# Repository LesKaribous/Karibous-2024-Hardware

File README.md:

# Karibous-2024-Hardware
Hardware du robot des Karibous pour la Coupe de Robotique (Eurobot) 2024

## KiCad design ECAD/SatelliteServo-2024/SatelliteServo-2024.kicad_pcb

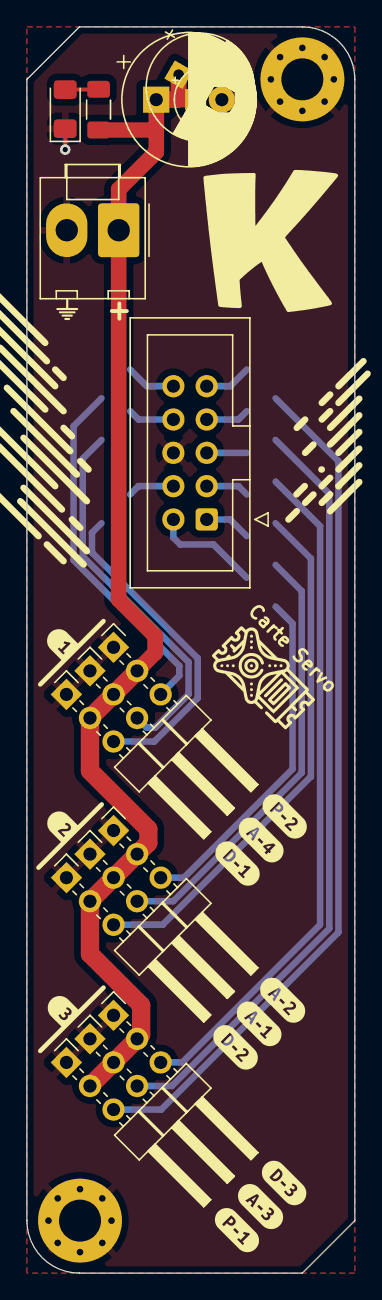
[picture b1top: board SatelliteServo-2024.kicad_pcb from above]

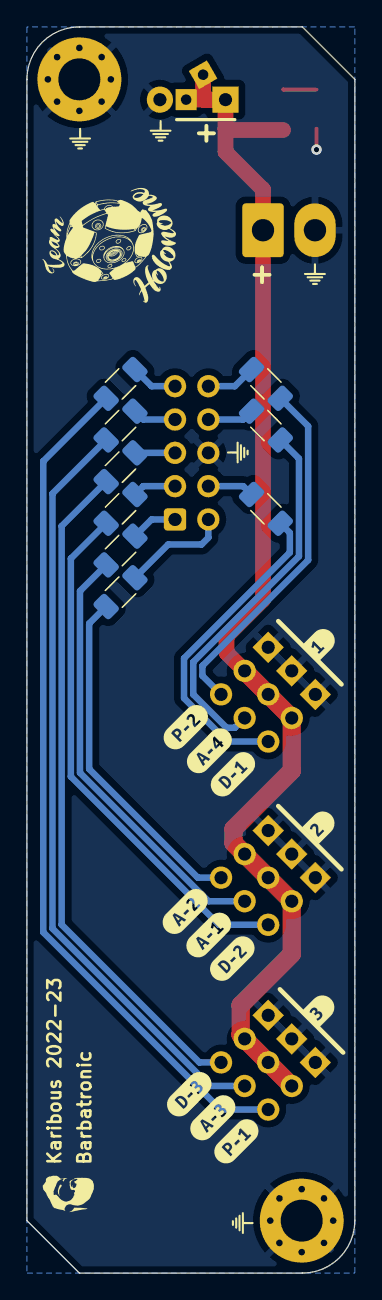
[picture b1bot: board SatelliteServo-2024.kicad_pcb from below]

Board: 2 copper layers, 25.0 x 95.0 mm, 51 parts (21 on the bottom side), 21 nets.

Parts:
C1: C_Polarized_Small; CP_Radial_D10.0mm_P5.00mm
C2: C_Polarized_Small; CP_Radial_D8.0mm_P3.80mm
C3: C_Polarized_Small; CP_Radial_D5.0mm_P2.00mm
D1: LED_Small; LED_1206_3216Metric_Pad1.42x1.75mm_HandSolder
H1, H2: MountingHole_Pad; MountingHole_3.2mm_M3_Pad_Via
J1: Conn_02x05_Odd_Even; IDC-Header_2x05_P2.54mm_Vertical
J2: Conn_01x02; Molex_KK-396_A-41791-0002_1x02_P3.96mm_Vertical
J3, J4, J5, J6, J7, J8, J9, J10, J11: Conn_01x03; PinHeader_3x01_P2.54mm_Horizontal
R1: R_Small; R_1206_3216Metric_Pad1.30x1.75mm_HandSolder
R2, R3, R4, R5, R6, R7, R8, R9, R10: 220; R_1206_3216Metric_Pad1.30x1.75mm_HandSolder
kibuzzard-634F1A03, kibuzzard-634F1A03#2: G***; kibuzzard-634F1A03
kibuzzard-634F1A09, kibuzzard-634F1A09#2: G***; kibuzzard-634F1A09
kibuzzard-634F1B5B: G***; kibuzzard-634F1B5B
kibuzzard-634F1B38: G***; kibuzzard-634F1B38
kibuzzard-634F1B56: G***; kibuzzard-634F1B56
kibuzzard-634F1BA4: G***; kibuzzard-634F1BA4
kibuzzard-634F1BAB: G***; kibuzzard-634F1BAB
kibuzzard-634F1BB2: G***; kibuzzard-634F1BB2
kibuzzard-634F18D6, kibuzzard-634F18D6#2: G***; kibuzzard-634F18D6
kibuzzard-634F18FE, kibuzzard-634F18FE#2: G***; kibuzzard-634F18FE
kibuzzard-634F19A0, kibuzzard-634F19A0#2: G***; kibuzzard-634F19A0
kibuzzard-634F19A7, kibuzzard-634F19A7#2: G***; kibuzzard-634F19A7
kibuzzard-634F19AD, kibuzzard-634F19AD#2: G***; kibuzzard-634F19AD
kibuzzard-634F19FE, kibuzzard-634F19FE#2: G***; kibuzzard-634F19FE
kibuzzard-634F1907, kibuzzard-634F1907#2: G***; kibuzzard-634F1907

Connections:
+5VP: C1.1, C2.1, C3.1, J2.1, J3.2, J4.2, J5.2, J6.2, J7.2, J8.2, J9.2, J10.2, J11.2, R1.1
GND: C1.2, C2.2, C3.2, D1.1 (K), H1.1, H2.1, J1.6, J2.2, J3.1, J4.1, J5.1, J6.1, J7.1, J8.1, J9.1, J10.1, J11.1
IO_A_1: J1.1, R7.2
IO_A_2: J1.2, R8.2
IO_A_3: J1.7, R9.2
IO_A_4: J1.8, R10.2
IO_D_1: J1.4, R2.2
IO_D_2: J1.3, R3.2
IO_D_3: J1.5, R4.2
IO_P_1: J1.9, R5.2
IO_P_2: J1.10, R6.2
unnamed: D1.2 (A), R1.2
unnamed: J3.3, R2.1
unnamed: J4.3, R3.1
unnamed: J5.3, R4.1
unnamed: J6.3, R7.1
unnamed: J7.3, R5.1
unnamed: J8.3, R6.1
unnamed: J9.3, R8.1
unnamed: J10.3, R9.1
unnamed: J11.3, R10.1

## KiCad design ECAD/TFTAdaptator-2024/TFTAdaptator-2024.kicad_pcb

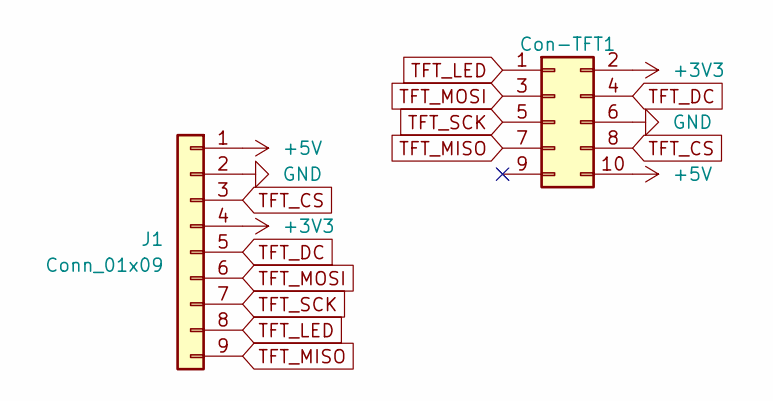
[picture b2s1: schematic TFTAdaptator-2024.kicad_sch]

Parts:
Con-TFT1: Conn_02x05_Odd_Even; IDC-Header_2x05_P2.54mm_Vertical
J1: Conn_01x09; PinSocket_1x09_P2.54mm_Vertical

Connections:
+3V3: Con-TFT1.2, J1.4
+5V: Con-TFT1.10, J1.1
GND: Con-TFT1.6, J1.2
TFT_CS: Con-TFT1.8, J1.3
TFT_DC: Con-TFT1.4, J1.5
TFT_LED: Con-TFT1.1, J1.8
TFT_MISO: Con-TFT1.7, J1.9
TFT_MOSI: Con-TFT1.3, J1.6
TFT_SCK: Con-TFT1.5, J1.7

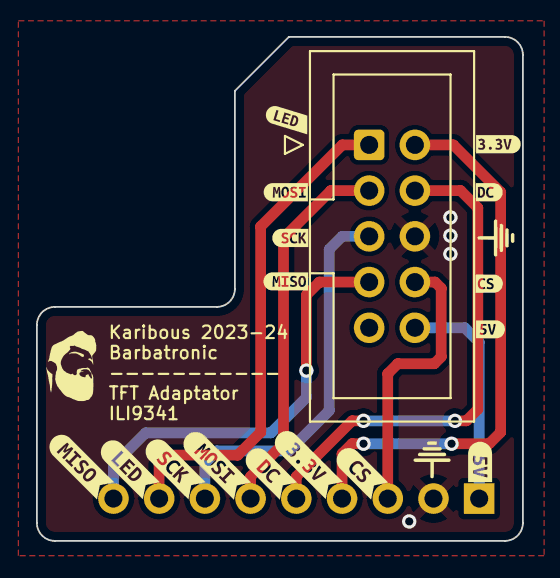
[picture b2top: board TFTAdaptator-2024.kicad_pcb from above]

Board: 2 copper layers, 27.0 x 28.0 mm, 18 parts (1 on the bottom side), 9 nets.

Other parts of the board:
kibuzzard-64E9C8A2: G***; kibuzzard-64E9C8A2
kibuzzard-64E9C89C: G***; kibuzzard-64E9C89C
kibuzzard-64E9C866: G***; kibuzzard-64E9C866
kibuzzard-64E9C890: G***; kibuzzard-64E9C890
kibuzzard-64E9C897: G***; kibuzzard-64E9C897
kibuzzard-64E9CBF9: G***; kibuzzard-64E9CBF9
kibuzzard-64E9CDB6: G***; kibuzzard-64E9CDB6
kibuzzard-64E9CDBF: G***; kibuzzard-64E9CDBF
kibuzzard-64E9CDD4: G***; kibuzzard-64E9CDD4
kibuzzard-64E9CDE3: G***; kibuzzard-64E9CDE3
kibuzzard-64E9CE8E: G***; kibuzzard-64E9CE8E
kibuzzard-64E9CE87: G***; kibuzzard-64E9CE87
kibuzzard-64E9CE93: G***; kibuzzard-64E9CE93
kibuzzard-64E9CEBE: G***; kibuzzard-64E9CEBE
kibuzzard-64E9CFC9: G***; kibuzzard-64E9CFC9
kibuzzard-64933136: G***; kibuzzard-64933136

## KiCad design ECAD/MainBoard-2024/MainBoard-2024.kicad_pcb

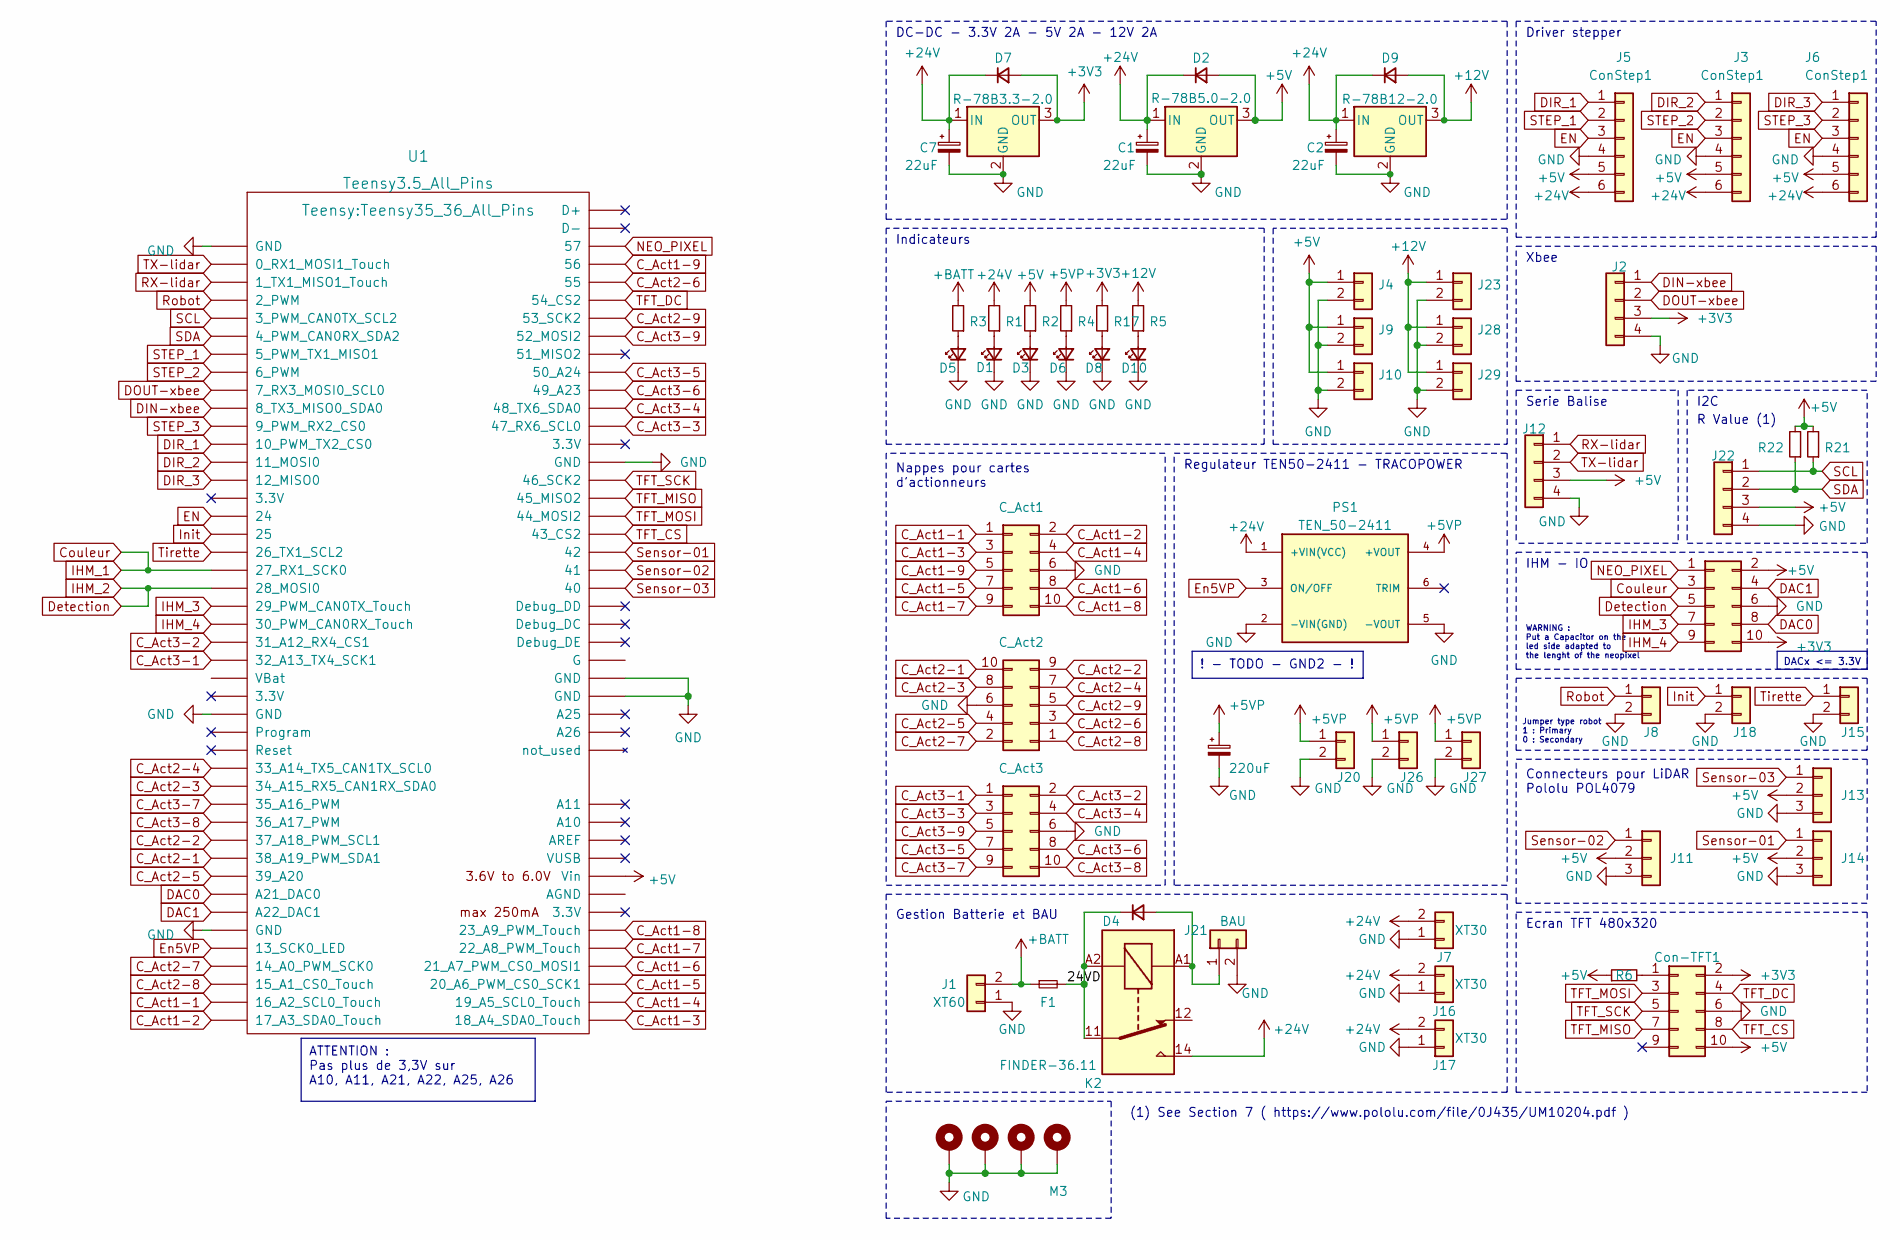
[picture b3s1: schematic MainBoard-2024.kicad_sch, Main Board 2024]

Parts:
C1, C2, C7: 22uF; CP_Elec_5x5.4
C6: 220uF; CP_Radial_D8.0mm_P3.80mm
C_Act1, C_Act2, C_Act3: Conn_02x05_Odd_Even; IDC-Header_2x05_P2.54mm_Vertical
Con-TFT1: Conn_02x05_Odd_Even; IDC-Header_2x05_P2.54mm_Vertical
D1, D3, D5, D6, D8, D10: LED_Small; LED_1206_3216Metric_Pad1.42x1.75mm_HandSolder
D2, D4, D7, D9: D_Small; D_SMA_Handsoldering
F1: Fuse_Small; Fuseholder_Blade_Mini_Keystone_3568
H1, H2, H3, H4: M3; MountingHole_3.2mm_M3_Pad_Via
IHM-IO1: Conn_02x05_Odd_Even; IDC-Header_2x05_P2.54mm_Vertical
J1: XT60; AMASS_XT60-M_1x02_P7.20mm_Vertical
J2, J12, J22: Conn_01x04; Molex_KK-254_AE-6410-04A_1x04_P2.54mm_Vertical
J3, J5, J6: ConStep1; Molex_KK-254_AE-6410-06A_1x06_P2.54mm_Vertical
J4, J9, J10, J15, J18, J23, J28, J29: Conn_01x02; Molex_KK-254_AE-6410-02A_1x02_P2.54mm_Vertical
J7, J16, J17: XT30; AMASS_XT30U-F_1x02_P5.0mm_Vertical
J8: Conn_01x02; PinHeader_1x02_P2.54mm_Vertical
J11, J13, J14: Conn_01x03; Molex_KK-254_AE-6410-03A_1x03_P2.54mm_Vertical
J20, J21, J26, J27: BAU; Molex_KK-396_A-41791-0002_1x02_P3.96mm_Vertical
K2: FINDER-36.11; Relay_SPDT_Finder_36.11
PS1: TEN_50-2411; CONV_TEN_50-2411; PARTREV February 3, 2021
R1, R2, R3, R4, R5, R6, R17, R21, R22: R_Small; R_1206_3216Metric_Pad1.30x1.75mm_HandSolder
U1: Teensy3.5_All_Pins; Teensy35_36_All_Pins
U2: R-78B3.3-2.0; Converter_DCDC_RECOM_R-78B-2.0_THT
U3: R-78B12-2.0; Converter_DCDC_RECOM_R-78B-2.0_THT
U4: R-78B5.0-2.0; Converter_DCDC_RECOM_R-78B-2.0_THT

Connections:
+3V3: Con-TFT1.2, D7.2 (A), IHM-IO1.10, J2.3, R17.2, U2.3 (OUT)
+5V: Con-TFT1.10, D2.2 (A), IHM-IO1.2, J3.5, J4.1, J5.5, J6.5, J9.1, J10.1, J11.2, J12.3, J13.2, J14.2, J22.3, R2.2, R6.1, R21.2, R22.2, U1.53 (Vin), U4.3 (OUT)
+5VP: C6.1, J20.1, J26.1, J27.1, PS1.4 (+VOUT), R4.2
+12V: D9.2 (A), J23.1, J28.1, J29.1, R5.2, U3.3 (OUT)
+24V: C1.1, C2.1, C7.1, D2.1 (K), D7.1 (K), D9.1 (K), J3.6, J5.6, J6.6, J7.2, J16.2, J17.2, K2.14, PS1.1 (+VIN(VCC)), R1.2, U2.1 (IN), U3.1 (IN), U4.1 (IN)
+BATT: F1.1, J1.2, R3.2
/24VD: D4.1 (K), F1.2, K2.11, K2.A2
C_Act1-1: C_Act1.1, U1.43 (16_A2_SCL0_Touch)
C_Act1-2: C_Act1.2, U1.44 (17_A3_SDA0_Touch)
C_Act1-3: C_Act1.3, U1.45 (18_A4_SDA0_Touch)
C_Act1-4: C_Act1.4, U1.46 (19_A5_SCL0_Touch)
C_Act1-5: C_Act1.7, U1.47 (20_A6_PWM_CS0_SCK1)
C_Act1-6: C_Act1.8, U1.48 (21_A7_PWM_CS0_MOSI1)
C_Act1-7: C_Act1.9, U1.49 (22_A8_PWM_Touch)
C_Act1-8: C_Act1.10, U1.50 (23_A9_PWM_Touch)
C_Act1-9: C_Act1.5, U1.85 (56)
C_Act2-1: C_Act2.10, U1.35 (38_A19_PWM_SDA1)
C_Act2-2: C_Act2.9, U1.34 (37_A18_PWM_SCL1)
C_Act2-3: C_Act2.8, U1.31 (34_A15_RX5_CAN1RX_SDA0)
C_Act2-4: C_Act2.7, U1.30 (33_A14_TX5_CAN1TX_SCL0)
C_Act2-5: C_Act2.4, U1.36 (39_A20)
C_Act2-6: C_Act2.3, U1.84 (55)
C_Act2-7: C_Act2.2, U1.41 (14_A0_PWM_SCK0)
C_Act2-8: C_Act2.1, U1.42 (15_A1_CS0_Touch)
C_Act2-9: C_Act2.5, U1.82 (53_SCK2)
C_Act3-1: C_Act3.1, U1.24 (32_A13_TX4_SCK1)
C_Act3-2: C_Act3.2, U1.23 (31_A12_RX4_CS1)
C_Act3-3: C_Act3.3, U1.76 (47_RX6_SCL0)
C_Act3-4: C_Act3.4, U1.77 (48_TX6_SDA0)
C_Act3-5: C_Act3.7, U1.79 (50_A24)
C_Act3-6: C_Act3.8, U1.78 (49_A23)
C_Act3-7: C_Act3.9, U1.32 (35_A16_PWM)
C_Act3-8: C_Act3.10, U1.33 (36_A17_PWM)
C_Act3-9: C_Act3.5, U1.81 (52_MOSI2)
Couleur: IHM-IO1.3, U1.19 (27_RX1_SCK0)
DAC0: IHM-IO1.8, U1.37 (A21_DAC0)
DAC1: IHM-IO1.4, U1.38 (A22_DAC1)
DIN-xbee: J2.1, U1.10 (8_TX3_MISO0_SDA0)
DIR_1: J5.1, U1.12 (10_PWM_TX2_CS0)
DIR_2: J3.1, U1.13 (11_MOSI0)
DIR_3: J6.1, U1.14 (12_MISO0)
DOUT-xbee: J2.2, U1.9 (7_RX3_MOSI0_SCL0)
Detection: IHM-IO1.5, U1.20 (28_MOSI0)
EN: J3.3, J5.3, J6.3, U1.16 (24)
En5VP: PS1.3 (ON/OFF), U1.40 (13_SCK0_LED)
GND: C1.2, C2.2, C6.2, C7.2, C_Act1.6, C_Act2.6, C_Act3.6, Con-TFT1.6, D1.1 (K), D3.1 (K), D5.1 (K), D6.1 (K), D8.1 (K), D10.1 (K), H1.1, H2.1, H3.1, H4.1, IHM-IO1.6, J1.1, J2.4, J3.4, J4.2, J5.4, J6.4, J7.1, J8.2, J9.2, J10.2, J11.3, J12.4, J13.3, J14.3, J15.2, J16.1, J17.1, J18.2, J20.2, J21.2, J22.4, J23.2, J26.2, J27.2, J28.2, J29.2, PS1.2 (-VIN(GND)), PS1.5 (-VOUT), U1.1 (GND), U1.27 (GND), U1.39 (GND), U1.61 (GND), U1.62 (GND), U1.74 (GND), U2.2 (GND), U3.2 (GND), U4.2 (GND)
IHM_3: IHM-IO1.7, U1.21 (29_PWM_CAN0TX_Touch)
IHM_4: IHM-IO1.9, U1.22 (30_PWM_CAN0RX_Touch)
Init: J18.1, U1.17 (25)
NEO_PIXEL: IHM-IO1.1, U1.86 (57)
unnamed: Con-TFT1.1, R6.2
unnamed: D1.2 (A), R1.1
unnamed: D3.2 (A), R2.1
unnamed: D4.2 (A), J21.1, K2.A1
unnamed: D5.2 (A), R3.1
unnamed: D6.2 (A), R4.1
unnamed: D8.2 (A), R17.1
unnamed: D10.2 (A), R5.1
RX-lidar: J12.1, U1.3 (1_TX1_MISO1_Touch)
Robot: J8.1, U1.4 (2_PWM)
SCL: J22.1, R21.1, U1.5 (3_PWM_CAN0TX_SCL2)
SDA: J22.2, R22.1, U1.6 (4_PWM_CAN0RX_SDA2)
STEP_1: J5.2, U1.7 (5_PWM_TX1_MISO1)
STEP_2: J3.2, U1.8 (6_PWM)
STEP_3: J6.2, U1.11 (9_PWM_RX2_CS0)
Sensor-01: J14.1, U1.69 (42)
Sensor-02: J11.1, U1.68 (41)
Sensor-03: J13.1, U1.67 (40)
TFT_CS: Con-TFT1.8, U1.70 (43_CS2)
TFT_DC: Con-TFT1.4, U1.83 (54_CS2)
TFT_MISO: Con-TFT1.7, U1.72 (45_MISO2)
TFT_MOSI: Con-TFT1.3, U1.71 (44_MOSI2)
TFT_SCK: Con-TFT1.5, U1.73 (46_SCK2)
TX-lidar: J12.2, U1.2 (0_RX1_MOSI1_Touch)
Tirette: J15.1, U1.18 (26_TX1_SCL2)

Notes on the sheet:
DACx <= 3.3V
ATTENTION : Pas plus de 3,3V sur A10, A11, A21, A22, A25, A26
! - TODO - GND2 - !
Nappes pour cartes d'actionneurs
Gestion Batterie et BAU
WARNING : Put a Capacitor on the led side adapted to the lenght of the neopixel
(1) See Section 7 ( https://www.pololu.com/file/0J435/UM10204.pdf )
Serie Balise
Connecteurs pour LiDAR Pololu POL4079
Jumper type robot 1 : Primary 0 : Secondary
Driver stepper
Xbee
Ecran TFT 480x320
DC-DC - 3.3V 2A - 5V 2A - 12V 2A
R Value (1)
Regulateur TEN50-2411 - TRACOPOWER
Indicateurs
IHM - IO
I2C

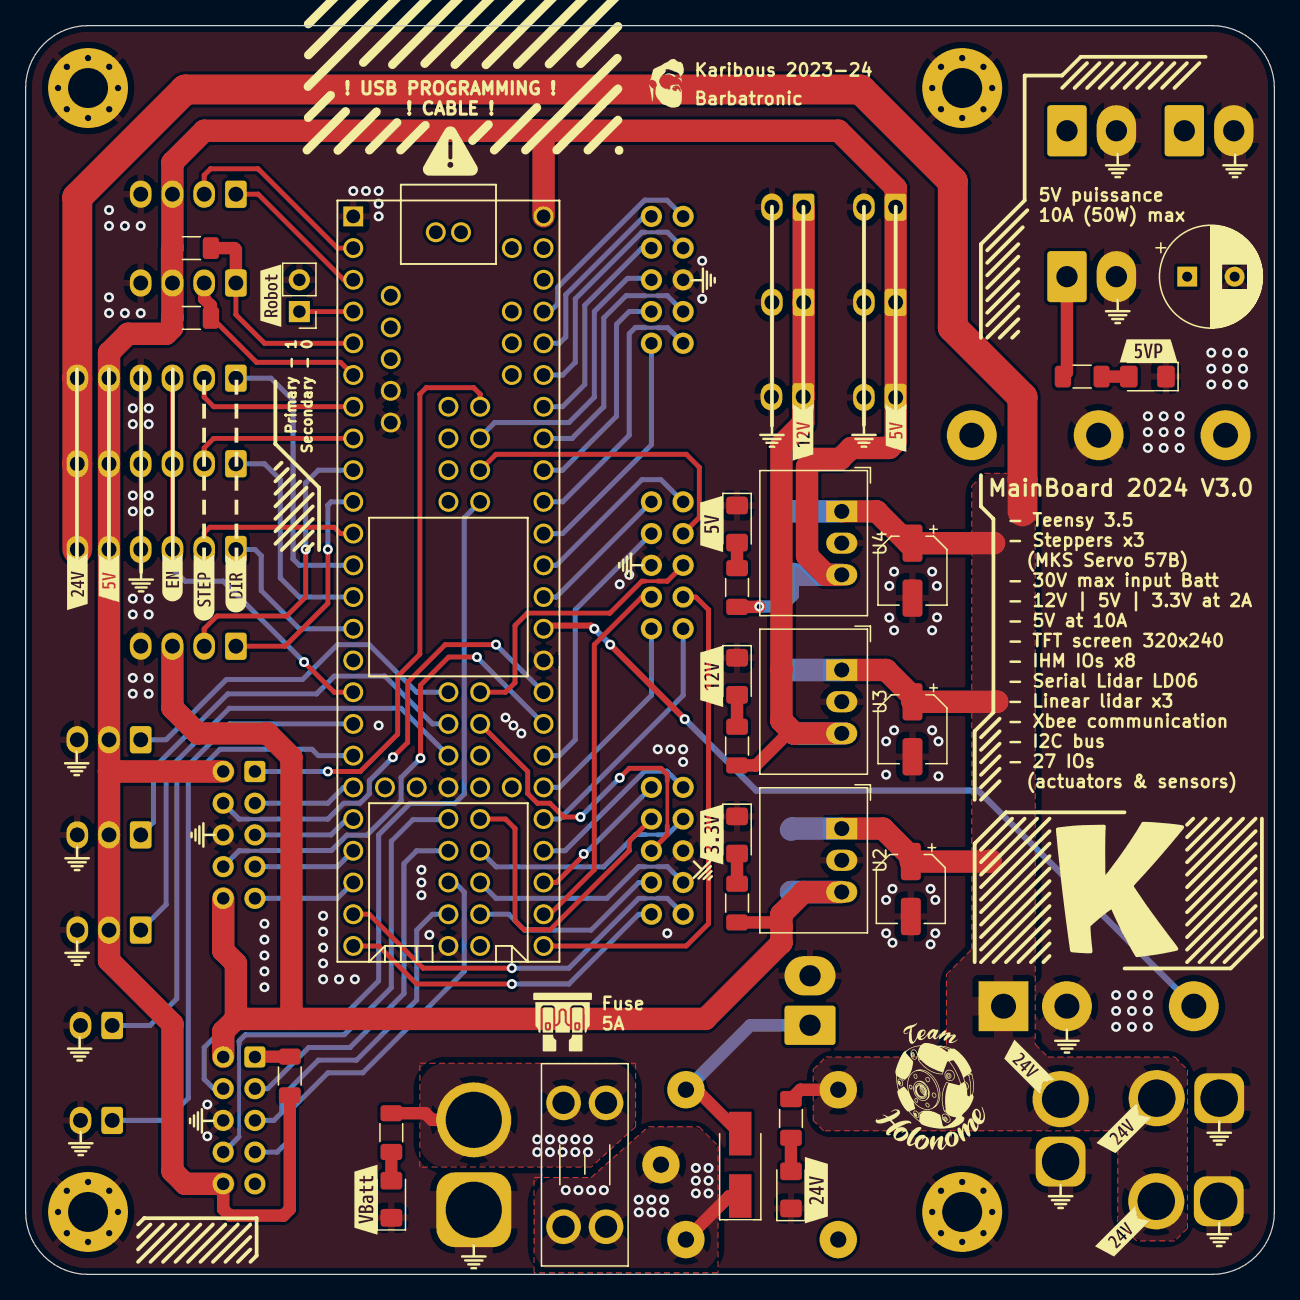
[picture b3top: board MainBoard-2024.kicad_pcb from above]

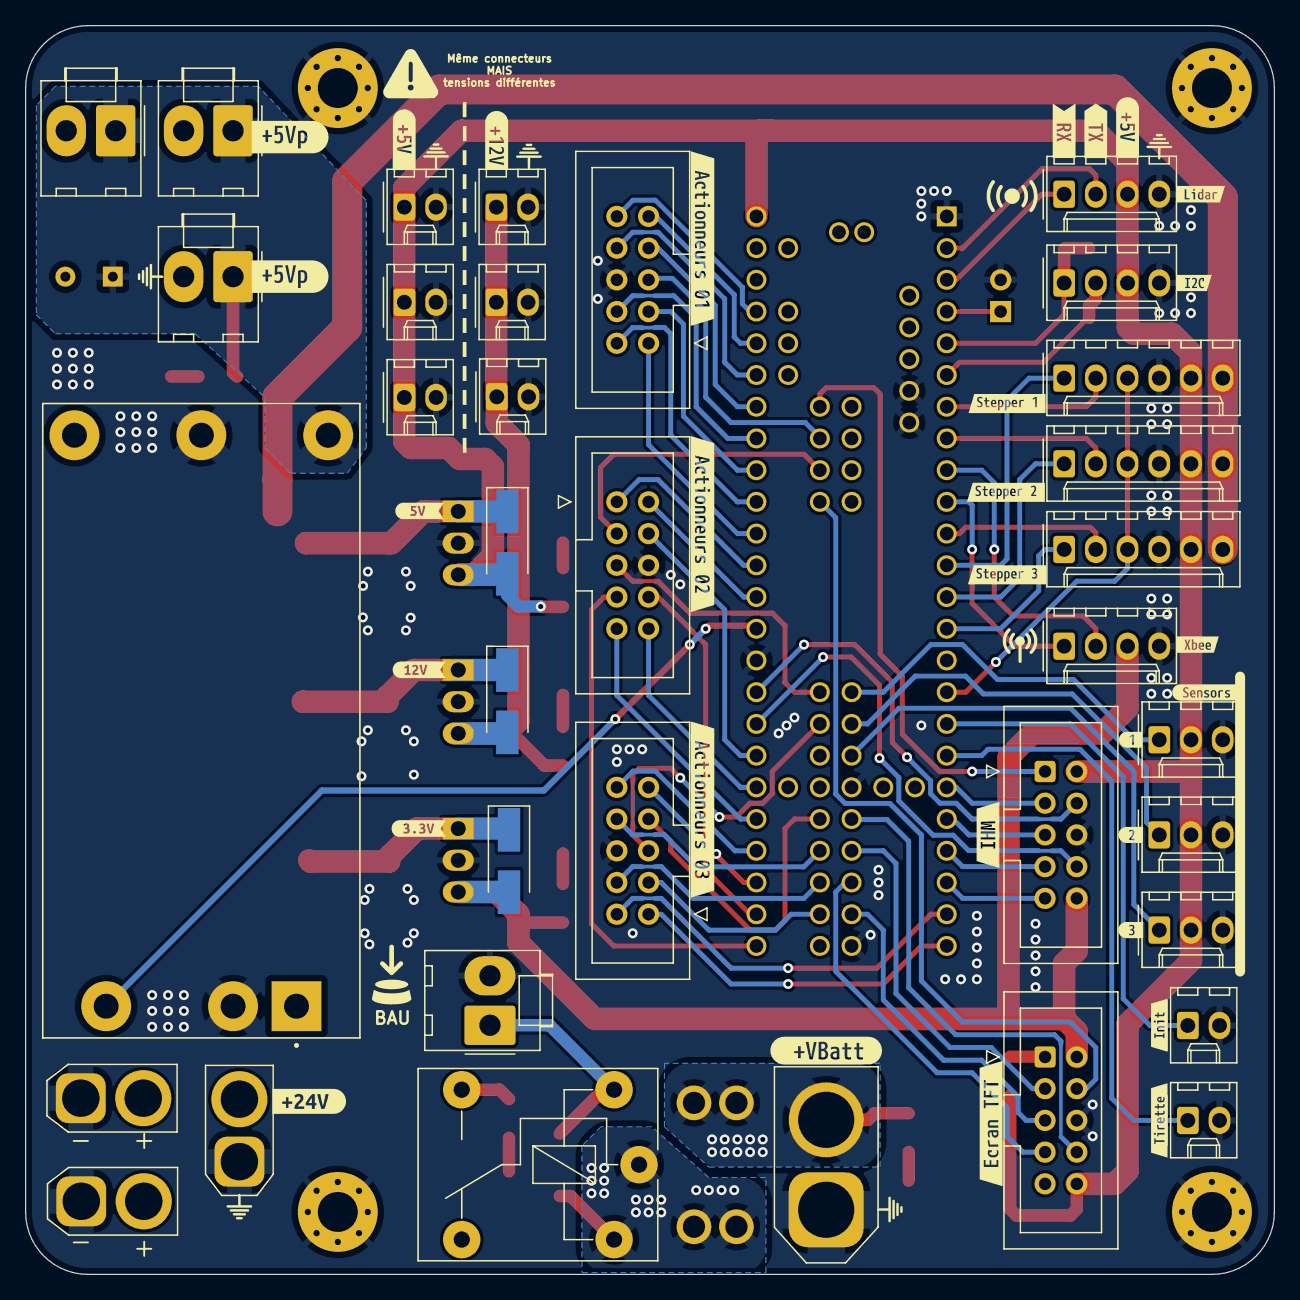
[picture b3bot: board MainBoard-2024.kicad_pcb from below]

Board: 2 copper layers, 100.0 x 100.0 mm, 111 parts (64 on the bottom side), 75 nets.

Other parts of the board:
kibuzzard-6493EE9E: G***; kibuzzard-6493EE9E
kibuzzard-6493EE40: G***; kibuzzard-6493EE40
kibuzzard-6493EE50: G***; kibuzzard-6493EE50
kibuzzard-6493EE56: G***; kibuzzard-6493EE56
kibuzzard-6493EE83: G***; kibuzzard-6493EE83
kibuzzard-6493EEAC: G***; kibuzzard-6493EEAC
kibuzzard-6493EEE0: G***; kibuzzard-6493EEE0
kibuzzard-6493EEF0: G***; kibuzzard-6493EEF0
kibuzzard-6493EF75: G***; kibuzzard-6493EF75
kibuzzard-6493EFD0: G***; kibuzzard-6493EFD0
kibuzzard-6493EFE7: G***; kibuzzard-6493EFE7
kibuzzard-6493EFEC: G***; kibuzzard-6493EFEC
kibuzzard-6493F0A8: G***; kibuzzard-6493F0A8
kibuzzard-6493F0C8: G***; kibuzzard-6493F0C8
kibuzzard-6493F0E7: G***; kibuzzard-6493F0E7
kibuzzard-6493F09E: G***; kibuzzard-6493F09E
kibuzzard-6493F18B: G***; kibuzzard-6493F18B
kibuzzard-6493F100: G***; kibuzzard-6493F100
kibuzzard-6493F174: G***; kibuzzard-6493F174
kibuzzard-6493F190: G***; kibuzzard-6493F190
kibuzzard-64932E55: G***; kibuzzard-64932E55
kibuzzard-64932EB2, kibuzzard-64932EB2#2: G***; kibuzzard-64932EB2
kibuzzard-64932F6F, kibuzzard-64932F6F#2: G***; kibuzzard-64932F6F
kibuzzard-64944CDF: G***; kibuzzard-64944CDF
kibuzzard-64944CEA: G***; kibuzzard-64944CEA
kibuzzard-64944CF9: G***; kibuzzard-64944CF9
kibuzzard-64944D19, kibuzzard-64944D19#2: G***; kibuzzard-64944D19
kibuzzard-64944D37, kibuzzard-64944D37#2, kibuzzard-64944D37#3, kibuzzard-64944D37#4: G***; kibuzzard-64944D37
kibuzzard-64944DAA: G***; kibuzzard-64944DAA
kibuzzard-649443C2: G***; kibuzzard-649443C2
kibuzzard-649443DA: G***; kibuzzard-649443DA
kibuzzard-649443F6: G***; kibuzzard-649443F6
kibuzzard-6494437E: G***; kibuzzard-6494437E
kibuzzard-6494443F: G***; kibuzzard-6494443F
kibuzzard-64933096: G***; kibuzzard-64933096
kibuzzard-64933122: G***; kibuzzard-64933122
kibuzzard-64933136: G***; kibuzzard-64933136
kibuzzard-64933140: G***; kibuzzard-64933140
kibuzzard-64944345: G***; kibuzzard-64944345
kibuzzard-64944398: G***; kibuzzard-64944398

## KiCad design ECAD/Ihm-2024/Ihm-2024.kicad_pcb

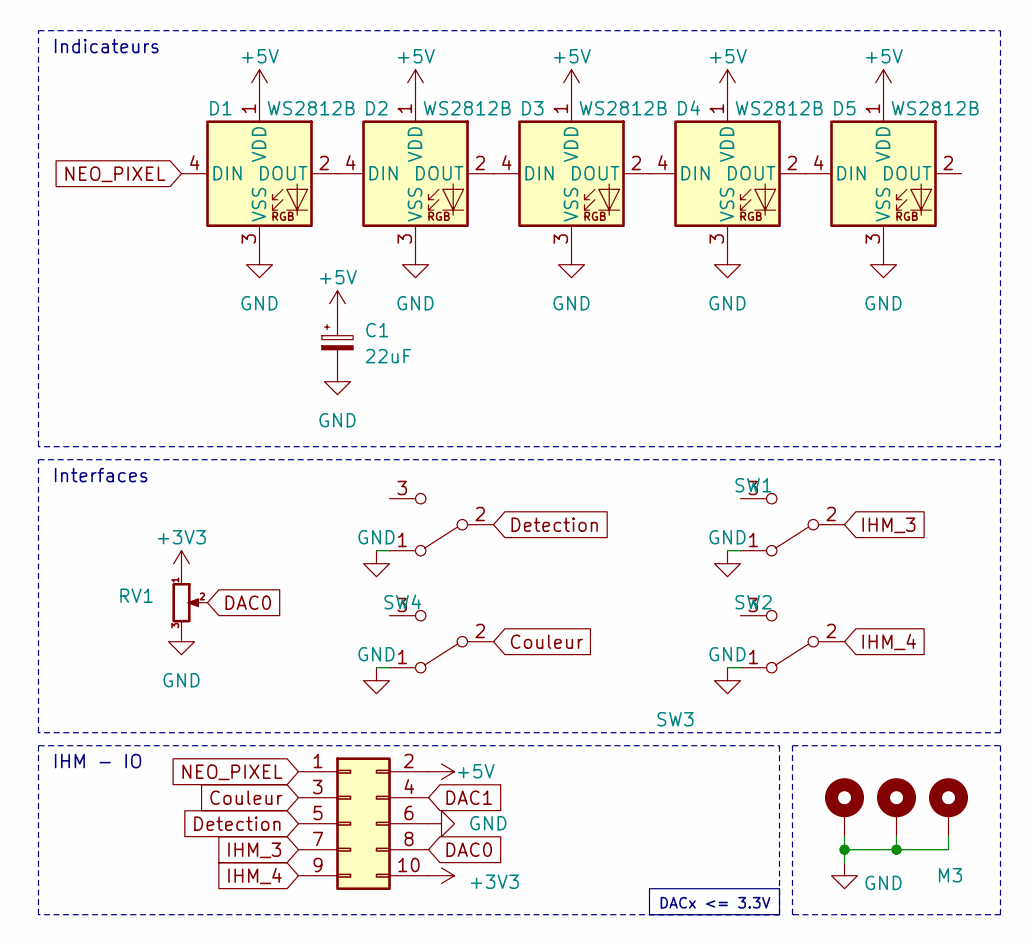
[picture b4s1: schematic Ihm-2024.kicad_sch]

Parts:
C1: 22uF; CP_Elec_5x5.4
D1, D2, D3, D4, D5: WS2812B; LED_WS2812B_PLCC4_5.0x5.0mm_P3.2mm
H1, H3, H4: M3; MountingHole_3.2mm_M3_Pad_Via
IHM-IO1: Conn_02x05_Odd_Even; IDC-Header_2x05_P2.54mm_Vertical
RV1: R_Potentiometer_Small; Potentiometer_Bourns_PTV09A-1_Single_Vertical
SW1, SW2, SW3, SW4: SW_SPDT; SK-12D10 1P2T

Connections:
+3V3: IHM-IO1.10, RV1.1
+5V: C1.1, D1.1 (VDD), D2.1 (VDD), D3.1 (VDD), D4.1 (VDD), D5.1 (VDD), IHM-IO1.2
Couleur: IHM-IO1.3, SW4.2 (B)
DAC0: IHM-IO1.8, RV1.2
DAC1: IHM-IO1.4
Detection: IHM-IO1.5, SW3.2 (B)
GND: C1.2, D1.3 (VSS), D2.3 (VSS), D3.3 (VSS), D4.3 (VSS), D5.3 (VSS), H1.1, H3.1, H4.1, IHM-IO1.6, RV1.3, SW1.1 (A), SW2.1 (A), SW3.1 (A), SW4.1 (A)
IHM_3: IHM-IO1.7, SW1.2 (B)
IHM_4: IHM-IO1.9, SW2.2 (B)
NEO_PIXEL: D1.4 (DIN), IHM-IO1.1
unnamed: D1.2 (DOUT), D2.4 (DIN)
unnamed: D2.2 (DOUT), D3.4 (DIN)
unnamed: D3.2 (DOUT), D4.4 (DIN)
unnamed: D4.2 (DOUT), D5.4 (DIN)

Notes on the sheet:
DACx <= 3.3V
Interfaces
IHM - IO
Indicateurs

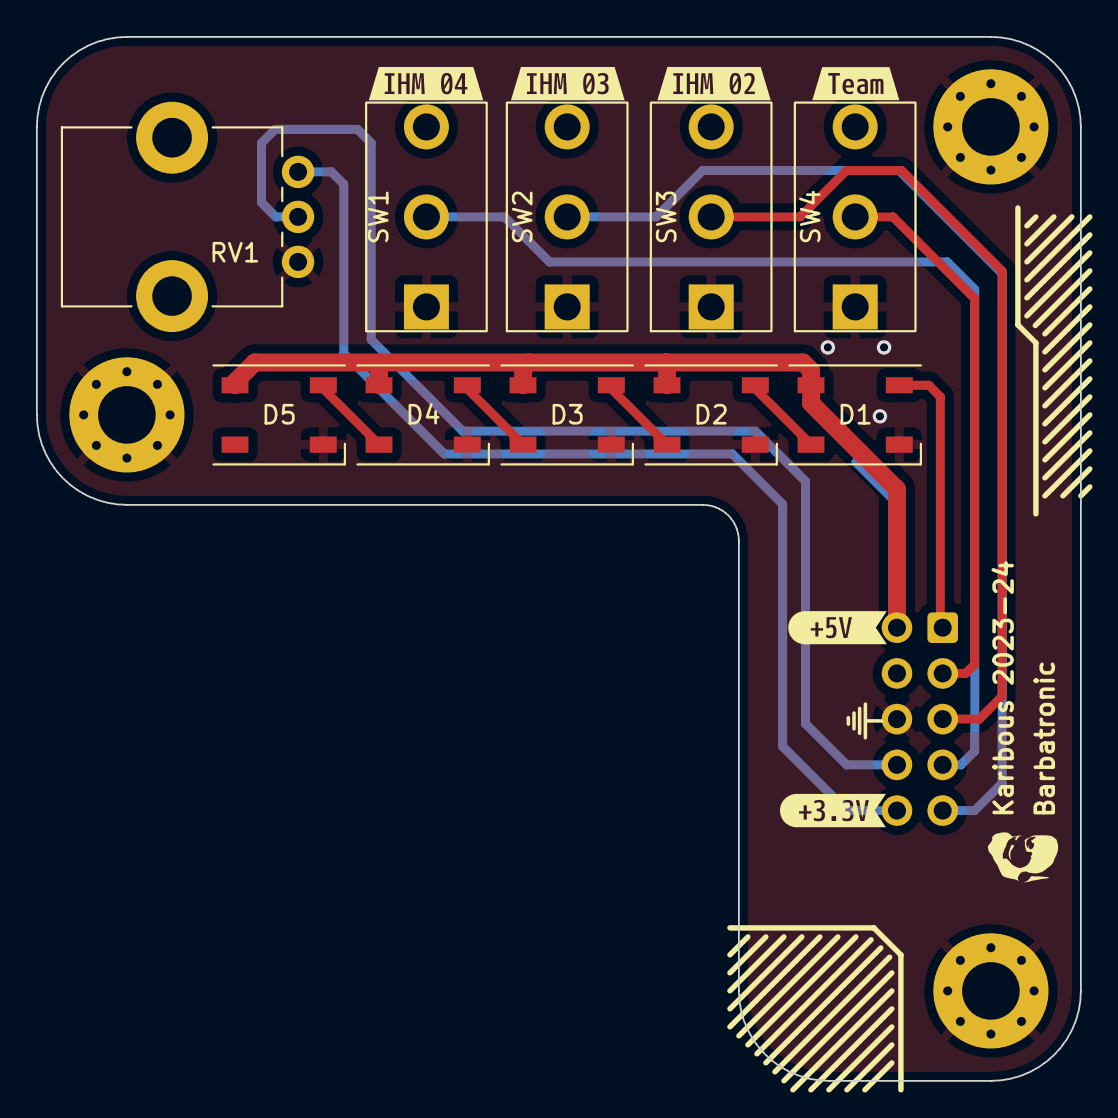
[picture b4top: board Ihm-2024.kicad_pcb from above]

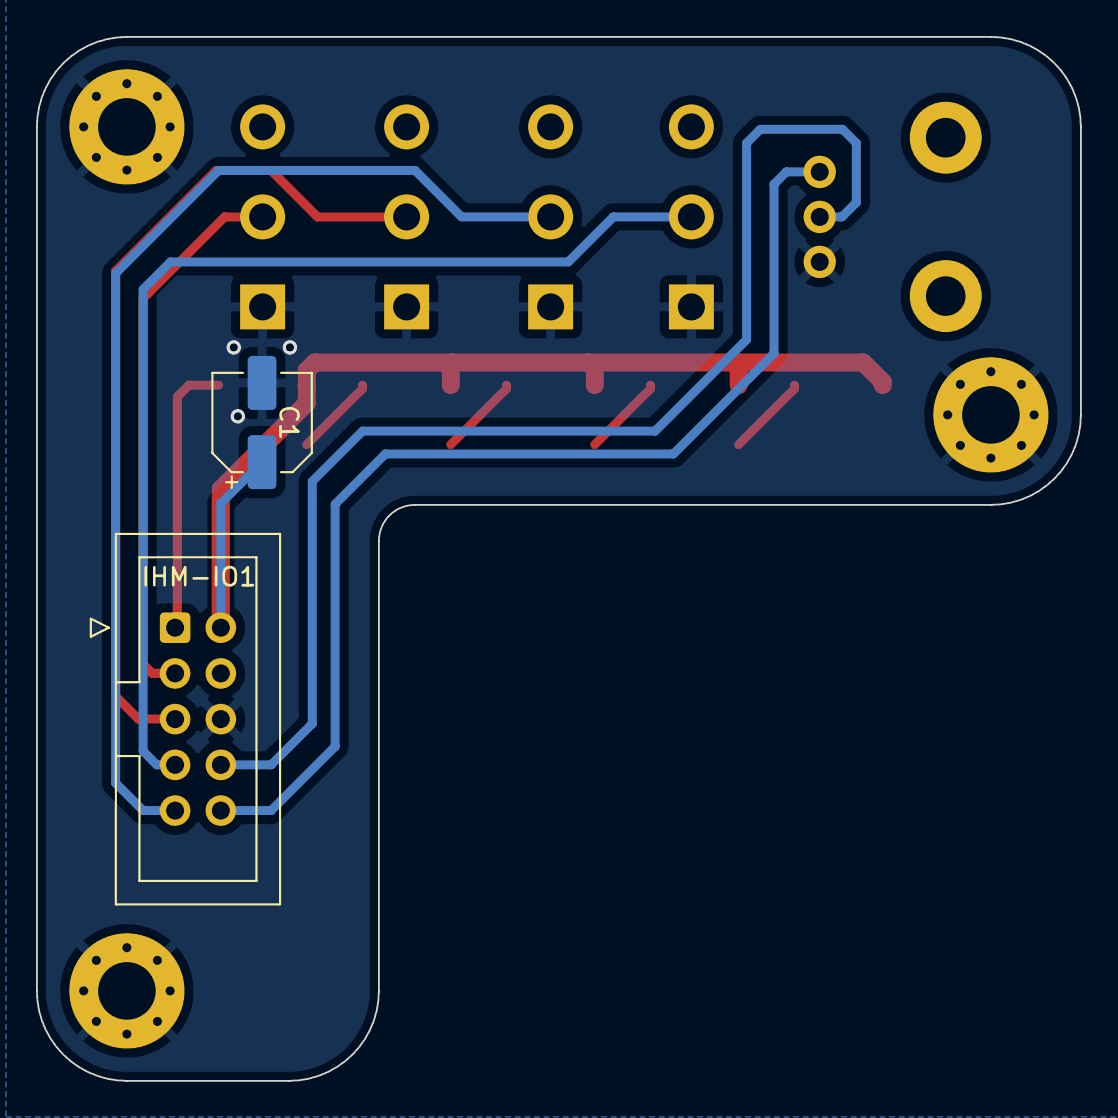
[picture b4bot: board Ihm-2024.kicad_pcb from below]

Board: 2 copper layers, 58.0 x 58.0 mm, 21 parts (2 on the bottom side), 13 nets.

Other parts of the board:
kibuzzard-64A1DF46: G***; kibuzzard-64A1DF46
kibuzzard-64A1DF73: G***; kibuzzard-64A1DF73
kibuzzard-64A1DFA1: G***; kibuzzard-64A1DFA1
kibuzzard-64A1DFBF: G***; kibuzzard-64A1DFBF
kibuzzard-64A1DFD1: G***; kibuzzard-64A1DFD1
kibuzzard-64A1DFD6: G***; kibuzzard-64A1DFD6

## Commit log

2023-05-28 MainBoard 2023 -> 2024
2023-05-29 Clean version MCAD for 2024
2023-06-04 change battery box - live 168
2023-06-08 update component and edge cut
2023-06-10 Simplify + add 12V regul
2023-06-10 change relay
2023-06-11 add ihm features and 12V connectores
2023-06-11 Update 3.3V connectors and placements
2023-06-12 Clean project
2023-06-12 add 3d files
2023-06-12 Backup
2023-06-12 Generate 3D view
2023-06-12 add FCStd1
2023-06-12 MainBoard integration
2023-06-12 Create PCB Ihm
2023-06-12 Multiple updates
    - Change connectors positions
    - Change Teensy position (for the USB port)
    - Add connector for init button
    - Add 5V signal on the Ihm connecto
2023-06-12 Update PCB integration
    - Change mainboard position
    - Add the TFT screen
    - Add the new Ihm PCB
    - Start V2 for Ihm
    - Clean some 2023 components
2023-06-12 update with PCB
2023-06-12 update with backups freecad files
2023-06-12 Re-arrange schematic
2023-06-14 Apply Aisler DRC 2 layer complex
2023-06-14 Apply Aisler DRC 2 layer simple
2023-06-21 First routing
2023-06-21 Clean positions
2023-06-21 First test trace
    PCB Trace with poor optimisation and bad width to check the board before final trace.
2023-06-21 Power trace routing
2023-06-21 fix trace width on actionneur connector
2023-06-21 fix trace width an position on IHM, TFT and side connectors
2023-06-21 Fix errors and warnings following DRC
2023-06-21 First silkscreen labels
2023-06-22 Complete Bottom Silkscreen
2023-06-22 update ICD connector
2023-06-22 Update Silkscreen
2023-06-22 add capacitor
2023-07-09 Live 170 - Carter IHM and TFT
2023-07-19 update battery cables and rapid carter
2023-07-22 fix recom 78b05 orientation
2023-08-02 fix gap on recom - Add vias
2023-08-02 fix nametag and vias before aisler order
2023-08-26 create TFT adaptator PCB
2023-08-26 update silkscreen, dimensions and DRC
2023-08-26 minor fix
2023-08-26 change resistor value
2023-08-26 minor change
2023-08-26 update gitignore
2023-08-26 clean repo
    Nettoyage du repo. La branche "backup-clean" a été créée pour conserver l'historique.
2023-09-15 create PAMI
2023-09-15 fix visual
2023-09-15 add silkscreen
2023-09-19 add BAU
2023-09-21 move PAMI to another repo
2023-09-23 Add 623zz
2023-10-20 Add vinyle and 2024 elements
2023-11-02 Add actuators
2023-11-02 add skeleton
2023-11-03 create actuators arms
2023-11-03 Add gripper on main actuators
2023-11-05 update proto actuator - live 180
2023-11-20 testing new gripper
2023-11-22 new bride gripper
2023-11-22 add fixations holes
2023-11-27 new test gripper
2024-01-02 archive the older actuator
2024-01-02 clean and archive
2024-01-02 new filaflex version
2024-01-02 clean, update and add flex actuator
2024-01-02 add new flex actuator and update perimeter
2024-01-02 nan
    Silly weird thing about update a complex file in freecad :D nothing to see here...
2024-01-02 add tubing gest
2024-01-14 add PCB Servo
2024-02-26 update battery clip and handle
2024-02-26 add Cable management for charging and programming
2024-02-27 upgrade Xbee support
2024-03-27 update hardware robot and table
2024-04-14 New Fork Actuators - Go Poseidon !
2024-04-19 before Belgium
2024-05-01 add balise ^^
2024-05-04 New actuator
2024-05-06 add features on beacon support
2024-05-06 esthetic updates
2024-05-09 WIP - new servo 2024 PCB
